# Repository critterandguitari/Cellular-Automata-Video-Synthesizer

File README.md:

Cellular-Automata-Video-Synthesizer
===================================

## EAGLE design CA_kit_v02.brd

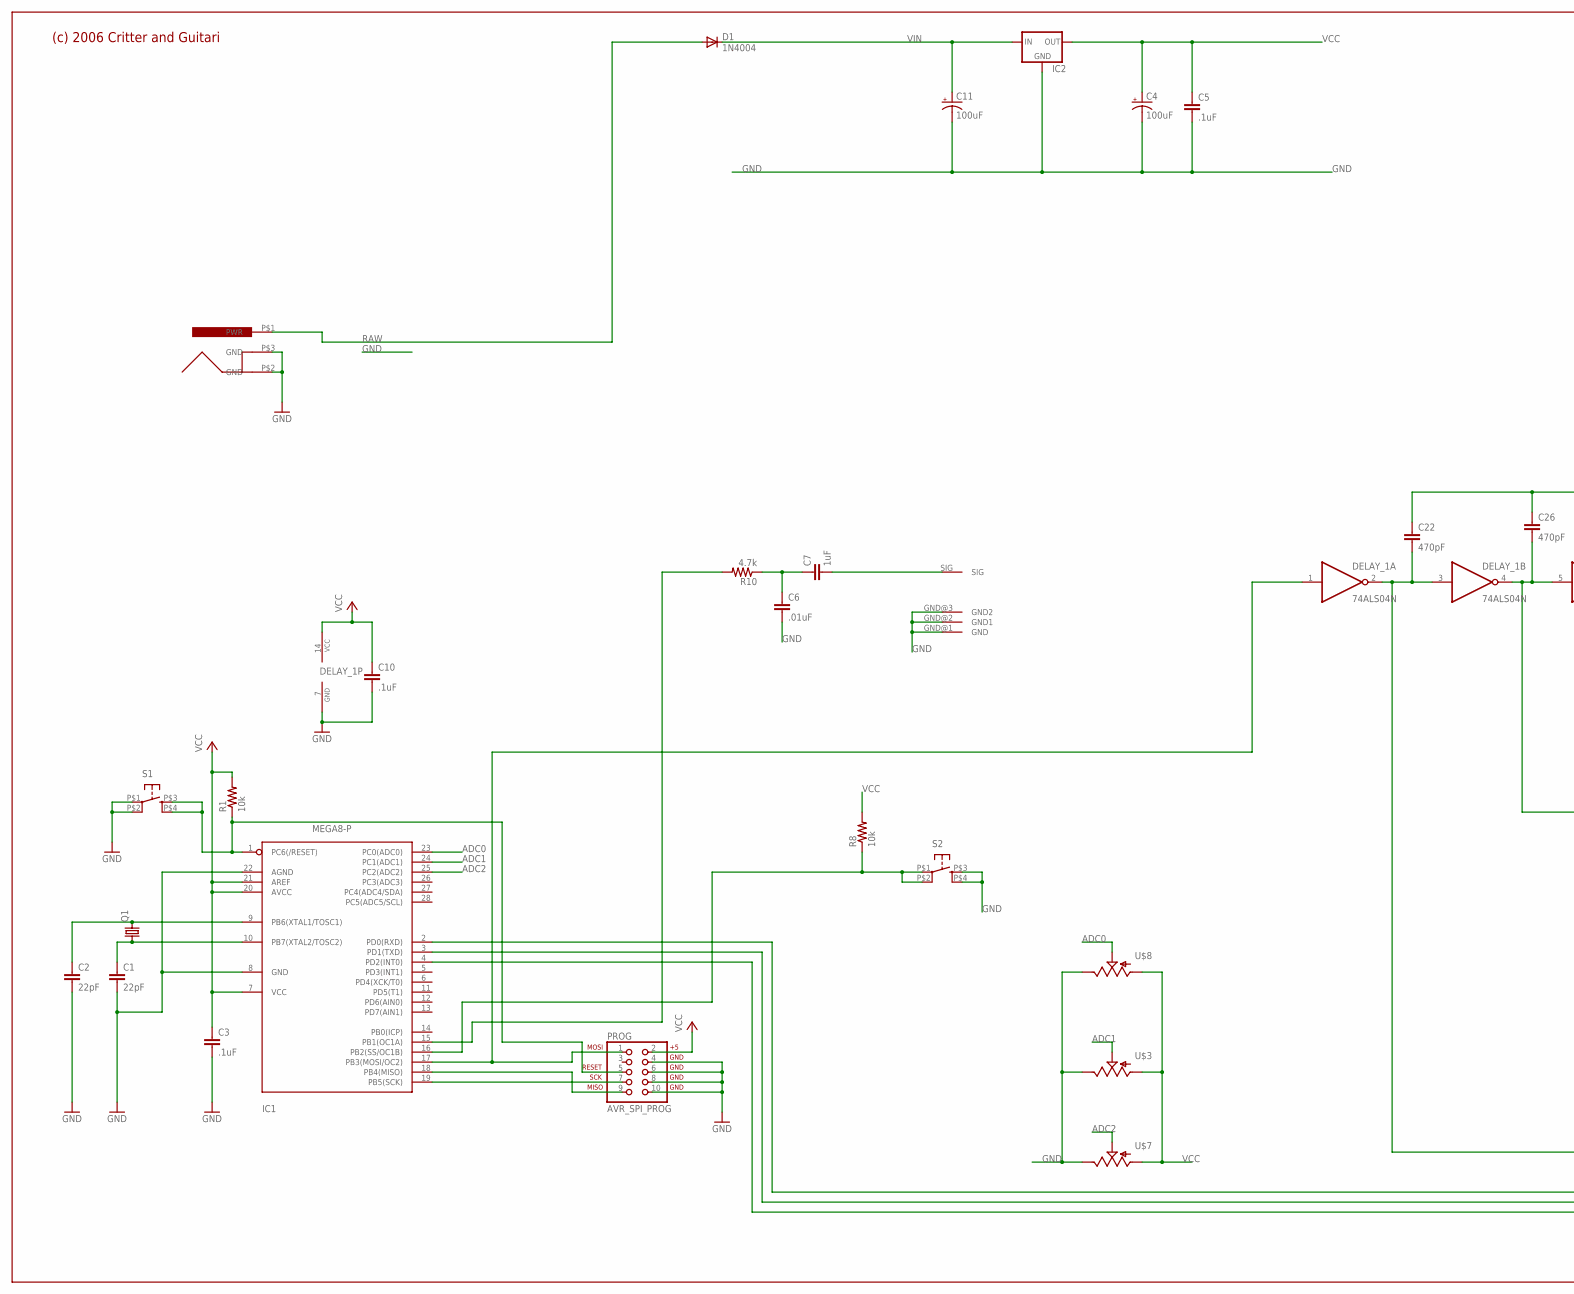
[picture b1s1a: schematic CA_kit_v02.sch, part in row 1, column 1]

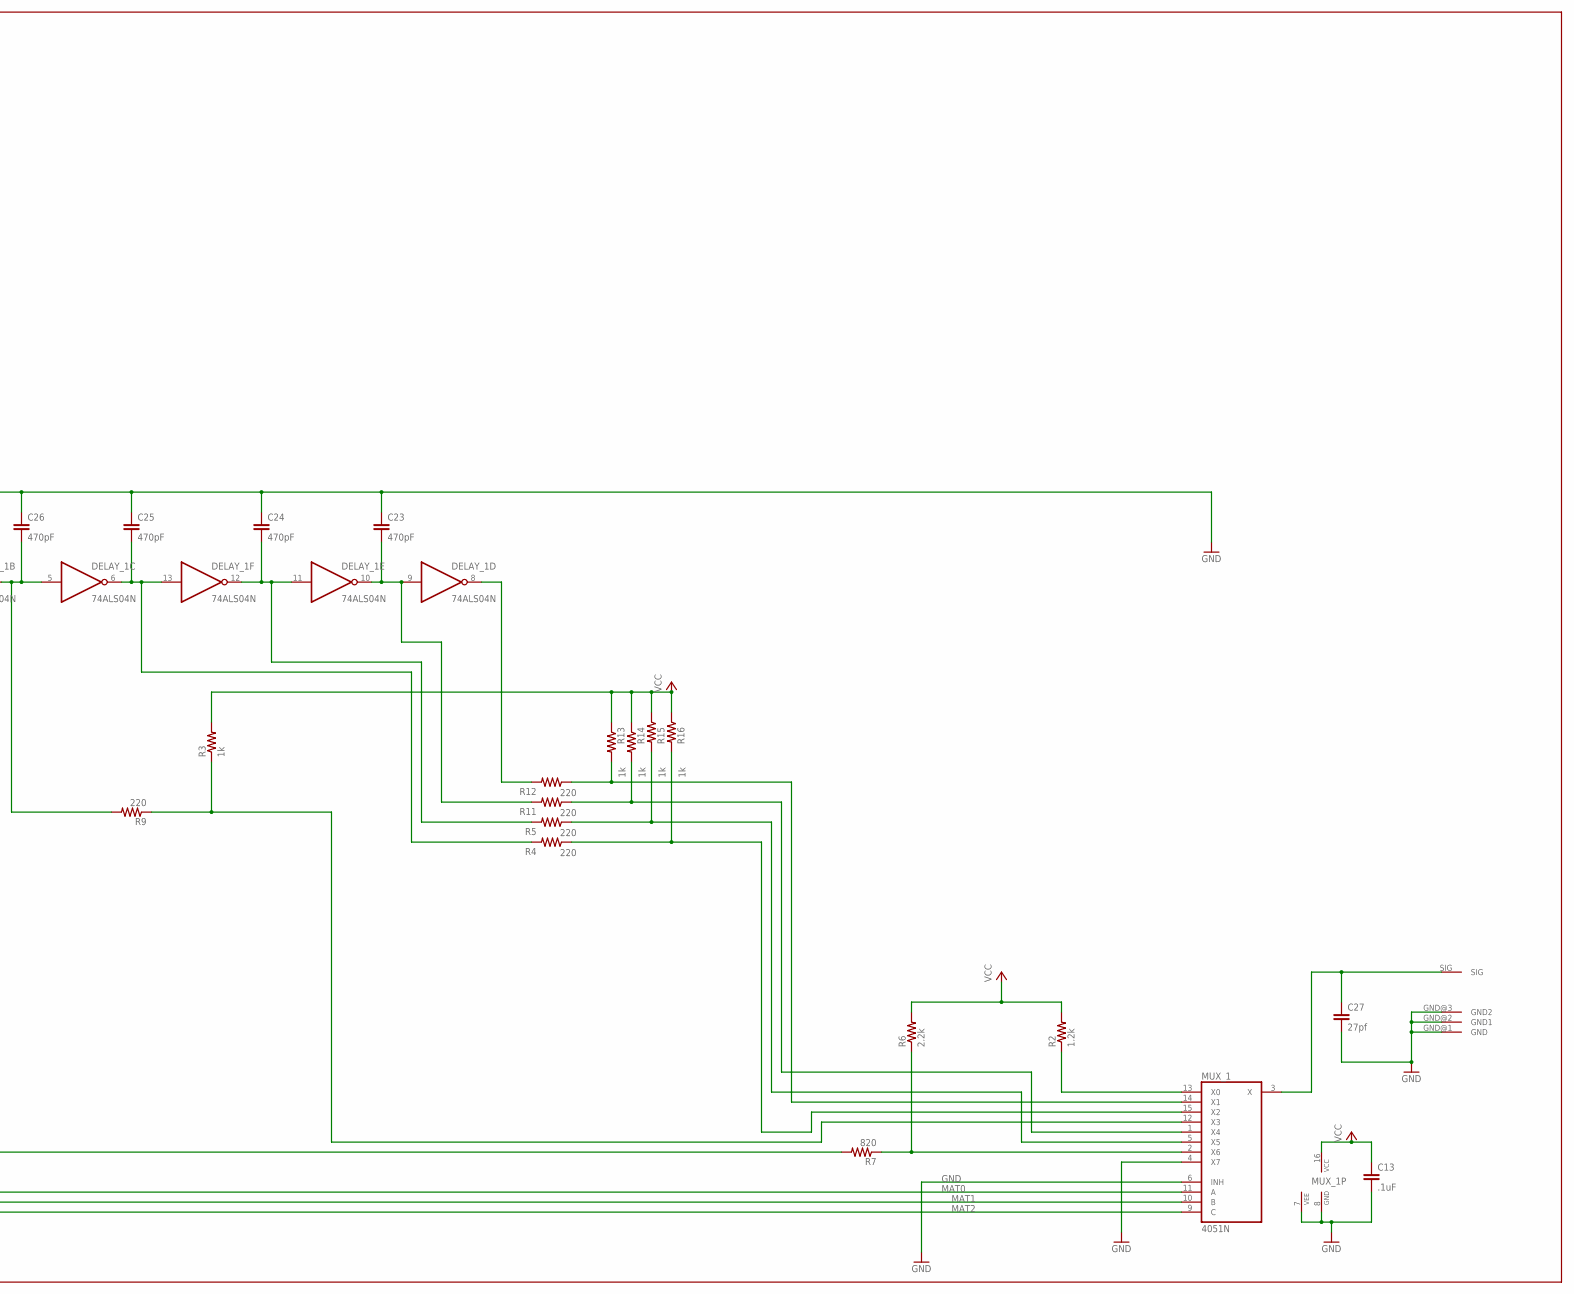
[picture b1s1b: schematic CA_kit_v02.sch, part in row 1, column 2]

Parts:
C1, C2: 22pF; C025-025X050
C3, C5, C10, C13: .1uF; C025-025X050
C4, C11: 100uF; E3,5-8
C6: .01uF; C025-025X050
C7: 1uF; C025-025X050
C22, C23, C24, C25, C26: 470pF; C025-025X050
C27: 27pf; C025-025X050
D1: 1N4004; DO41-10
DELAY_1: 74ALS04N; DIL14
IC1: MEGA8-P; DIL28-3
IC2: 78XXS
MUX_1: 4051N; DIL16
PROG: AVR_SPI_PROG; PINHEAD_2X05
Q1: CRYSTALHC49UV; HC49U-V
R1, R8: 10k; 0204V
R2: 1.2k; 0204V
R3, R13, R14, R15, R16: 1k; 0204V
R4, R5, R9, R11, R12: 220; 0204V
R6: 2.2k; 0204V
R7: 820; 0204V
R10: 4.7k; 0204V
S1, S2: TAC_SWITCHKSA_SEALED_TAC_SWITCH; KSA_SEALED_TAC_SWITCH
U$1: POWER_JACK
U$3, U$7, U$8: POT; ALPS_POT
U$5, U$6: PHONO_PLUG; PHONO_PCB

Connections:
ADC0: IC1.23 (PC0(ADC0)), U$8.P$2 (S)
ADC1: IC1.24 (PC1(ADC1)), U$3.P$2 (S)
ADC2: IC1.25 (PC2(ADC2)), U$7.P$2 (S)
BURST: C22.2, DELAY_1.2 (O), DELAY_1.3 (I), R7.2
COLORS: DELAY_1.1 (I), IC1.17 (PB3(MOSI/OC2)), PROG.1
GND: C1.2, C2.2, C3.2, C4.-, C5.2, C6.2, C10.2, C11.-, C13.2, C22.1, C23.1, C24.1, C25.1, C26.1, C27.2, DELAY_1.7 (GND), IC1.8 (GND), IC1.22 (AGND), IC2.GND, MUX_1.4 (X7), MUX_1.6 (INH), MUX_1.7 (VEE), MUX_1.8 (GND), PROG.4, PROG.6, PROG.8, PROG.10, S1.P$1, S1.P$2 (P1), S2.P$3 (S), S2.P$4 (S1), U$1.P$2 (GND), U$1.P$3 (GND), U$3.P$1 (E), U$5.GND@1 (GND), U$5.GND@2 (GND1), U$5.GND@3 (GND2), U$6.GND@1 (GND), U$6.GND@2 (GND1), U$6.GND@3 (GND2), U$7.P$1 (E), U$8.P$1 (E)
MAT0: IC1.2 (PD0(RXD)), MUX_1.11 (A)
MAT1: IC1.3 (PD1(TXD)), MUX_1.10 (B)
MAT2: IC1.4 (PD2(INT0)), MUX_1.9 (C)
unnamed: IC1.16 (PB2(SS/OC1B)), R8.1, S2.P$1, S2.P$2 (P1)
unnamed: DELAY_1.8 (O), R12.2
unnamed: C23.2, DELAY_1.9 (I), DELAY_1.10 (O), R11.2
unnamed: C2.1, IC1.9 (PB6(XTAL1/TOSC1)), Q1.2
unnamed: C1.1, IC1.10 (PB7(XTAL2/TOSC2)), Q1.1
unnamed: IC1.15 (PB1(OC1A)), R10.2
unnamed: C26.2, DELAY_1.4 (O), DELAY_1.5 (I), R9.2
unnamed: MUX_1.12 (X3), R3.1, R9.1
unnamed: C6.1, C7.1, R10.1
unnamed: IC1.1 (PC6(/RESET)), PROG.5, R1.1, S1.P$3 (S), S1.P$4 (S1)
unnamed: C7.2, U$5.SIG
unnamed: IC1.19 (PB5(SCK)), PROG.7
unnamed: IC1.18 (PB4(MISO)), PROG.9
unnamed: C25.2, DELAY_1.6 (O), DELAY_1.13 (I), R4.2
unnamed: C24.2, DELAY_1.11 (I), DELAY_1.12 (O), R5.2
unnamed: MUX_1.13 (X0), R2.1
unnamed: MUX_1.14 (X1), R12.1, R13.2
unnamed: MUX_1.1 (X4), R11.1, R14.2
unnamed: MUX_1.5 (X5), R5.1, R15.2
unnamed: MUX_1.15 (X2), R4.1, R16.2
unnamed: C27.1, MUX_1.3 (X), U$6.SIG
unnamed: MUX_1.2 (X6), R6.1, R7.1
RAW: D1.A, U$1.P$1 (PWR)
VCC: C3.1, C4.+, C5.1, C10.1, C13.1, DELAY_1.14 (VCC), IC1.7 (VCC), IC1.20 (AVCC), IC1.21 (AREF), IC2.OUT, MUX_1.16 (VCC), PROG.2, R1.2, R2.2, R3.2, R6.2, R8.2, R13.1, R14.1, R15.1, R16.1, U$3.P$3 (A), U$7.P$3 (A), U$8.P$3 (A)
VIN: C11.+, D1.C, IC2.IN

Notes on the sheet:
(c) 2006 Critter and Guitari

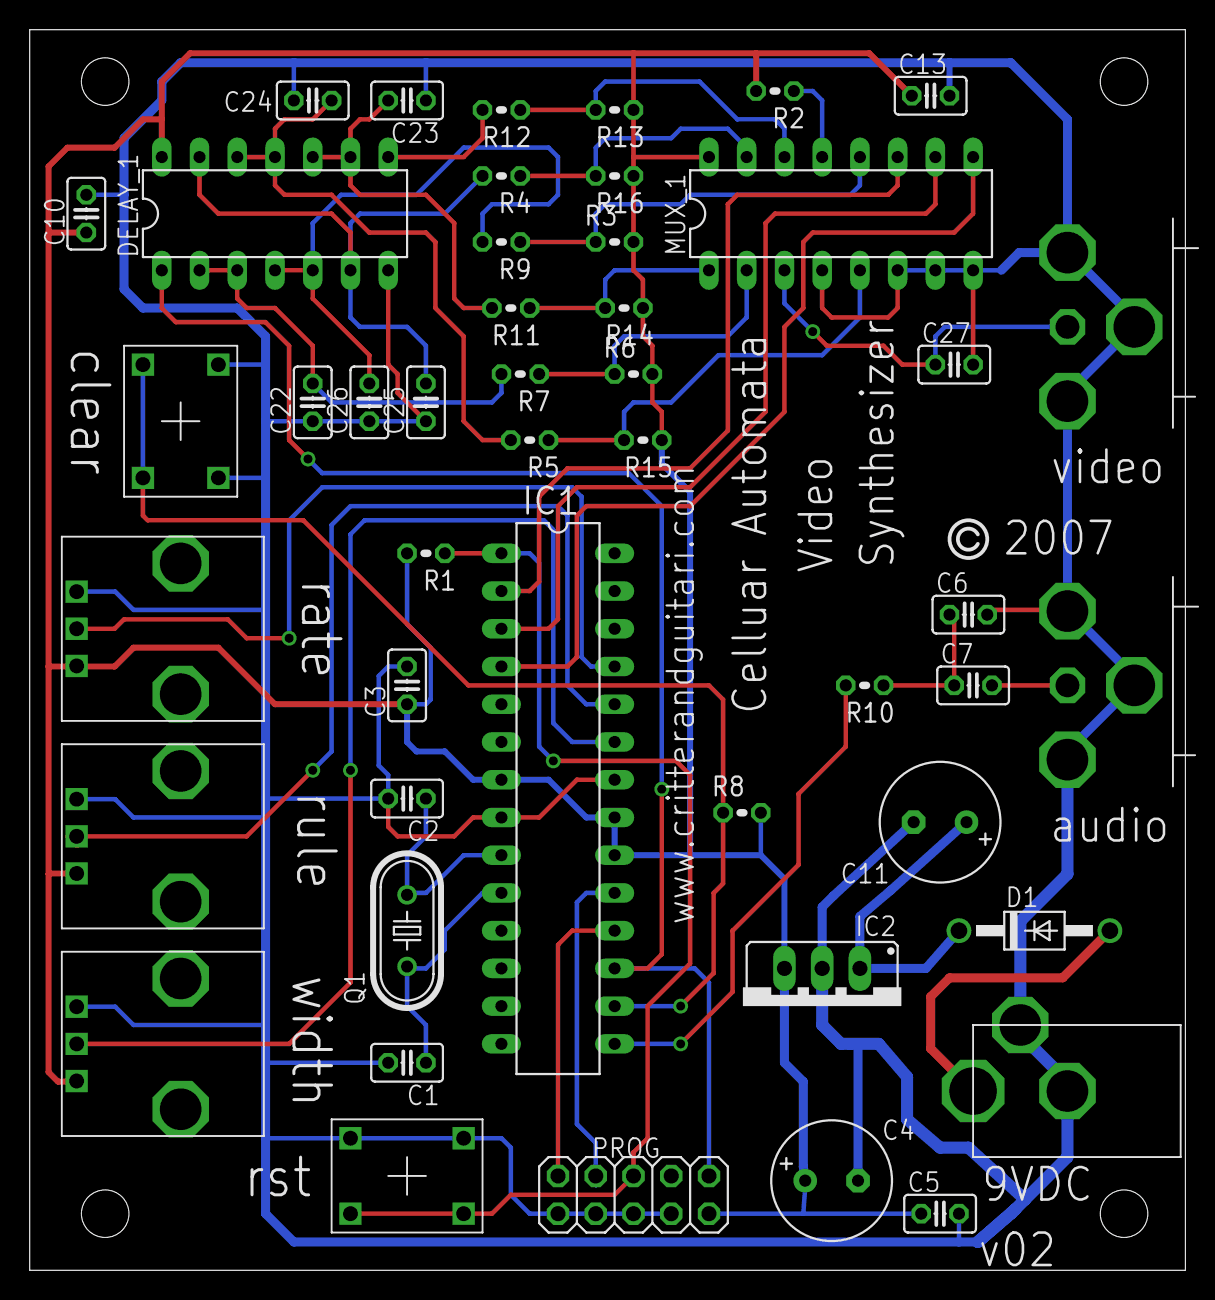
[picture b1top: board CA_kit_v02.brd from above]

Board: 2 copper layers, 77.8 x 83.5 mm, 47 parts (0 on the bottom side), 34 nets.

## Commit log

2013-04-21 adding eagle files
